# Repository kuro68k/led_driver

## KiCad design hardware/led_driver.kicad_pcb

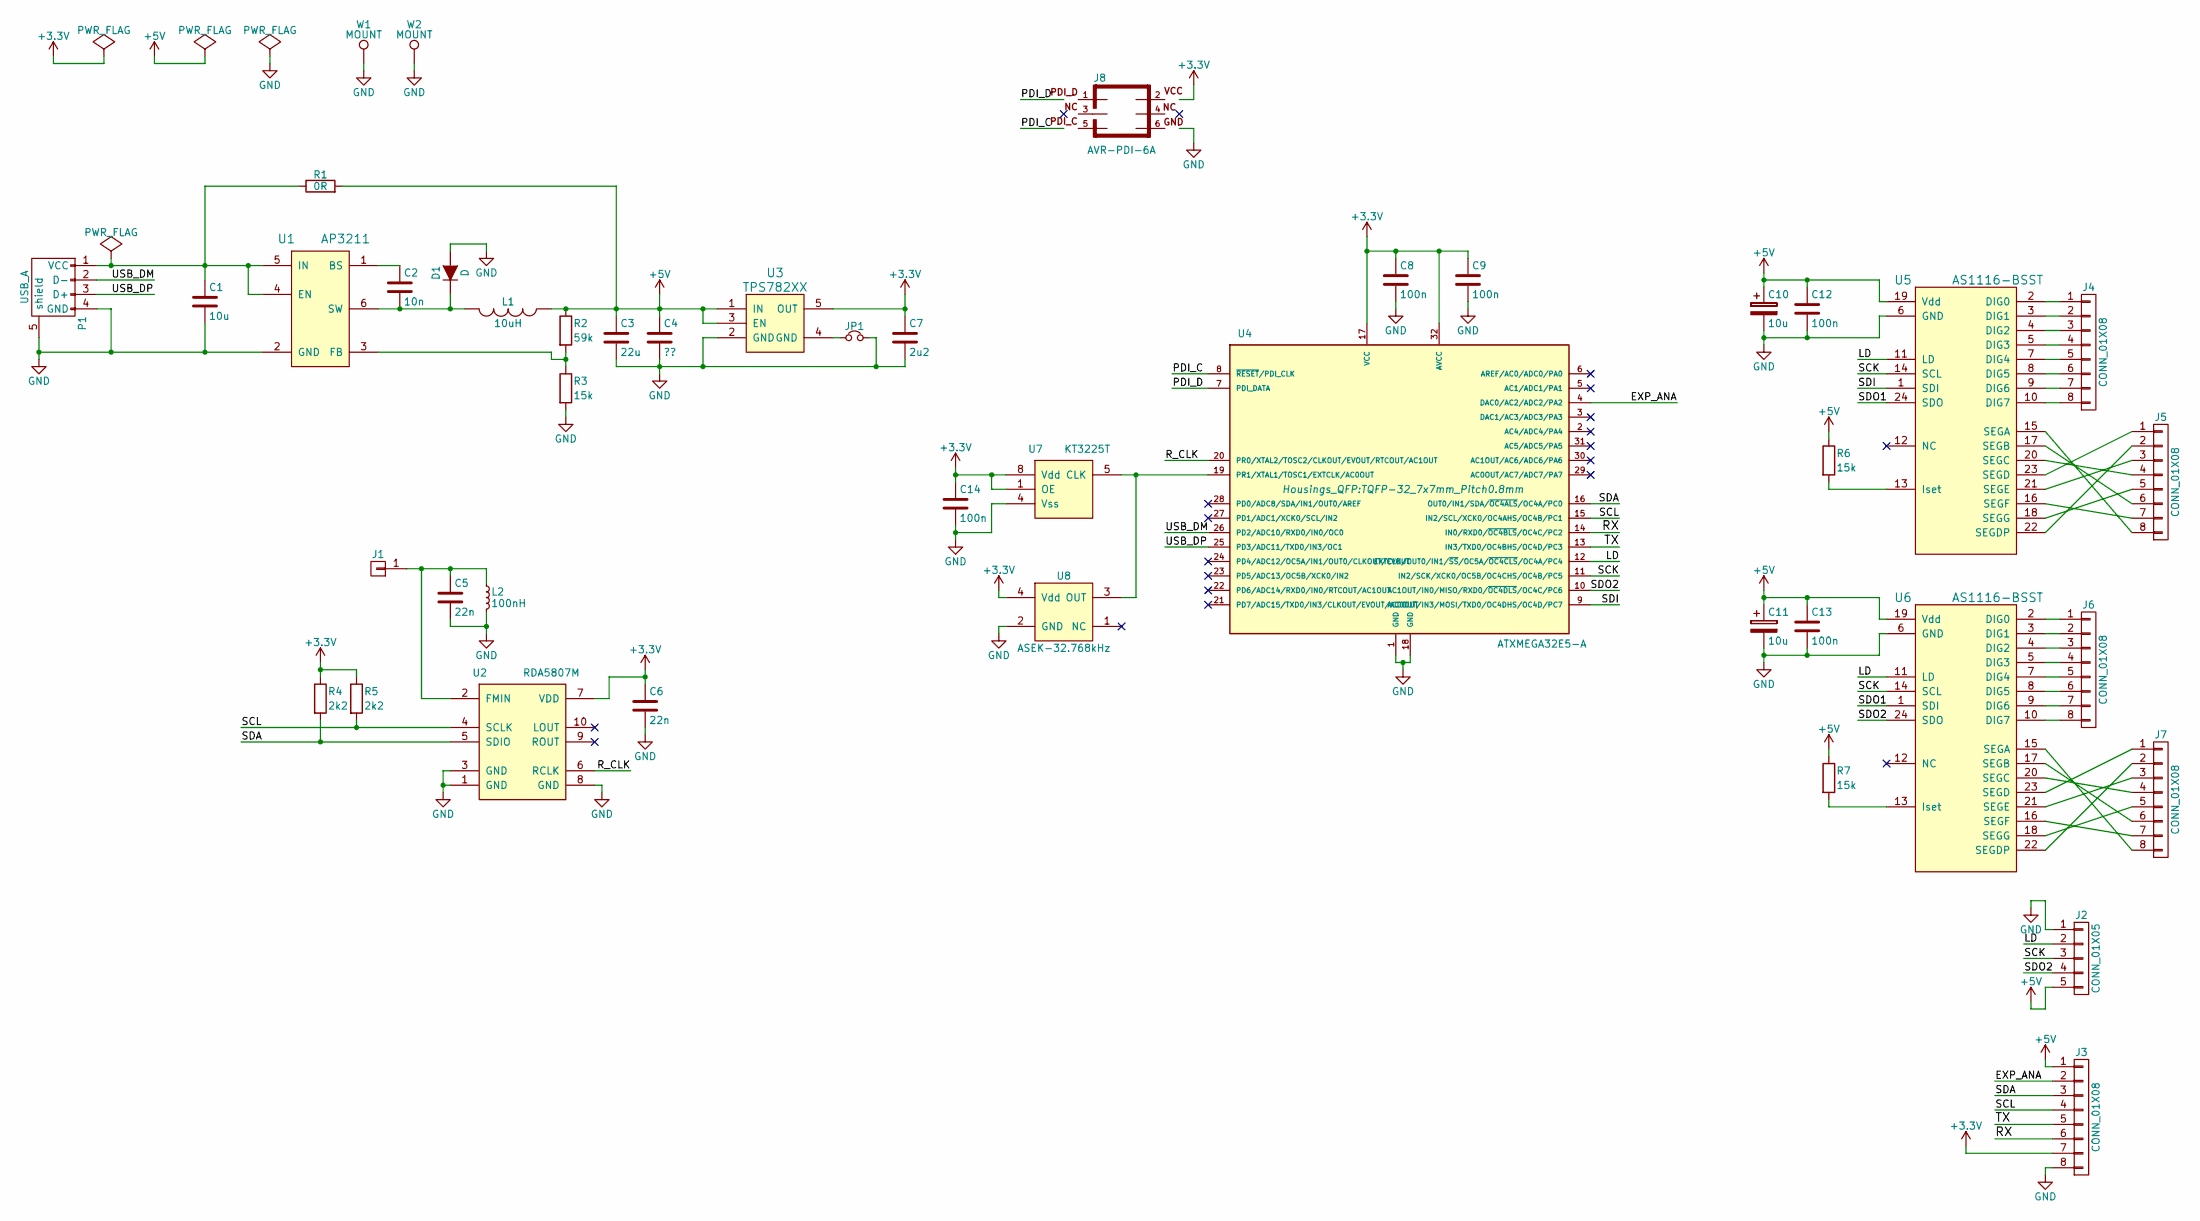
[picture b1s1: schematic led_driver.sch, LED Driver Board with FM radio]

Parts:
C1: 10u; C_0805
C2: 10n; C_0603
C3: 22u; C_0603
C4: ??; C_0603
C5, C6: 22n; C_0603
C7: 2u2; C_0603
C8, C9, C12, C13, C14: 100n; C_0603
C10, C11: 10u; SMD-1206_Pol
D1: D; SOD-323_HandSoldering
J1: CONN_01X01; Pin_Header_Straight_1x01
J2: CONN_01X05; B5B-ZR-SM4-TF
J3, J4, J5, J6, J7: CONN_01X08; B8B-ZR-SM4-TF
J8: AVR-PDI-6A; 3x2_1.27mm_SMD_header
JP1: Jumper_NC_Small; R_0603
L1: 10uH; Neosid_Inductor_SM-NE56_SMD2220
L2: 100nH; R_0603
P1: USB_A; Molex_47346-0001_Micro_USB_SMT
R1: 0R; R_0603
R2: 59k; R_0603
R3, R6, R7: 15k; R_0603
R4, R5: 2k2; R_0603
U1: AP3211; SOT-23-6
U2: RDA5807M; MSOP-10_3x3mm_Pitch0.5mm
U3: TPS782XX; SOT-23-5
U4: ATXMEGA32E5-A; TQFP-32_7x7mm_Pitch0.8mm
U5, U6: AS1116-BSST; SSOP-24_3.9x8.7mm_Pitch0.635mm
U7: KT3225T
U8: ASEK-32.768kHz; Crystal-3.2x2.5-ASEK-Series-Abracon
W1, W2: MOUNT; MountingHole_2.5mm_Pad

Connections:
+3V3: C6.1, C7.1, C8.1, C9.1, C14.1, J3.7, J8.2, R4.1, R5.1, U2.7 (VDD), U3.5 (OUT), U4.17 (VCC), U4.32 (AVCC), U7.1 (OE), U7.8 (Vdd), U8.4 (Vdd)
+5V: C3.1, C4.1, C10.1, C11.1, C12.1, C13.1, J2.5, J3.1, L1.1, R1.2, R2.1, R6.1, R7.1, U3.1 (IN), U3.3 (EN), U5.19 (Vdd), U6.19 (Vdd)
/EXP_ANA: J3.2, U4.4 (DAC0/AC2/ADC2/PA2)
/LD: J2.2, U4.12 (EXTCLK/OUT0/IN1/~SS~/OC5A/~OC4CLS~/OC4A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), U5.11 (LD), U6.11 (LD)
/PDI_C: J8.5, U4.8 (~RESET~/PDI_CLK)
/PDI_D: J8.1, U4.7 (PDI_DATA)
/RX: J3.6, U4.14 (IN0/RXD0/~OC4BLS~/OC4C/PC2)
/R_CLK: U2.6 (RCLK), U4.20 (PR0/XTAL2/TOSC2/CLKOUT/EVOUT/RTCOUT/AC1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)
/SCK: J2.3, U4.11 (IN2/SCK/XCK0/OC5B/OC4CHS/OC4B/PC5), U5.14 (SCL), U6.14 (SCL)
/SCL: J3.4, R5.2, U2.4 (SCLK), U4.15 (IN2/SCL/XCK0/OC4AHS/OC4B/PC1)
/SDA: J3.3, R4.2, U2.5 (SDIO), U4.16 (OUT0/IN1/SDA/~OC4ALS~/OC4A/PC0)
/SDI: U4.9 (AC0OUT/IN3/MOSI/TXD0/OC4DHS/OC4D/PC7), U5.1 (SDI)
/SDO1: U5.24 (SDO), U6.1 (SDI)
/SDO2: J2.4, U4.10 (AC1OUT/IN0/MISO/RXD0/~OC4DLS~/OC4C/PC6), U6.24 (SDO)
/TX: J3.5, U4.13 (IN3/TXD0/OC4BHS/OC4D/PC3)
/USB_DM: P1.2 (D-), U4.26 (PD2/ADC10/RXD0/IN0/OC0)
/USB_DP: P1.3 (D+), U4.25 (PD3/ADC11/TXD0/IN3/OC1)
GND: C1.2, C3.2, C4.2, C5.2, C6.2, C7.2, C8.2, C9.2, C10.2, C11.2, C12.2, C13.2, C14.2, D1.2 (A), J2.1, J3.8, J8.6, JP1.2, L2.2, P1.4 (GND), P1.5 (shield), R3.2, U1.2 (GND), U2.1 (GND), U2.3 (GND), U2.8 (GND), U3.2 (GND), U4.1 (GND), U4.18 (GND), U5.6 (GND), U6.6 (GND), U7.4 (Vss), U8.2 (GND), W1.1, W2.1
unnamed: C1.1, P1.1 (VCC), R1.1, U1.4 (EN), U1.5 (IN)
unnamed: C2.1, U1.1 (BS)
unnamed: C2.2, D1.1 (K), L1.2, U1.6 (SW)
unnamed: C5.1, J1.1, L2.1, U2.2 (FMIN)
unnamed: J4.1, U5.2 (DIG0)
unnamed: J4.2, U5.3 (DIG1)
unnamed: J4.3, U5.4 (DIG2)
unnamed: J4.4, U5.5 (DIG3)
unnamed: J4.5, U5.7 (DIG4)
unnamed: J4.6, U5.8 (DIG5)
unnamed: J4.7, U5.9 (DIG6)
unnamed: J4.8, U5.10 (DIG7)
unnamed: J5.1, U5.23 (SEGD)
unnamed: J5.2, U5.22 (SEGDP)
unnamed: J5.3, U5.21 (SEGE)
unnamed: J5.4, U5.20 (SEGC)
unnamed: J5.5, U5.18 (SEGG)
unnamed: J5.6, U5.17 (SEGB)
unnamed: J5.7, U5.16 (SEGF)
unnamed: J5.8, U5.15 (SEGA)
unnamed: J6.1, U6.2 (DIG0)
unnamed: J6.2, U6.3 (DIG1)
unnamed: J6.3, U6.4 (DIG2)
unnamed: J6.4, U6.5 (DIG3)
unnamed: J6.5, U6.7 (DIG4)
unnamed: J6.6, U6.8 (DIG5)
unnamed: J6.7, U6.9 (DIG6)
unnamed: J6.8, U6.10 (DIG7)
unnamed: J7.1, U6.23 (SEGD)
unnamed: J7.2, U6.22 (SEGDP)
unnamed: J7.3, U6.21 (SEGE)
unnamed: J7.4, U6.20 (SEGC)
unnamed: J7.5, U6.18 (SEGG)
unnamed: J7.6, U6.17 (SEGB)
unnamed: J7.7, U6.16 (SEGF)
unnamed: J7.8, U6.15 (SEGA)
unnamed: JP1.1, U3.4 (GND)
unnamed: R2.2, R3.1, U1.3 (FB)
unnamed: R6.2, U5.13 (Iset)
unnamed: R7.2, U6.13 (Iset)
unnamed: U4.19 (PR1/XTAL1/TOSC1/EXTCLK/AC0OUT), U7.5 (CLK), U8.3 (OUT)

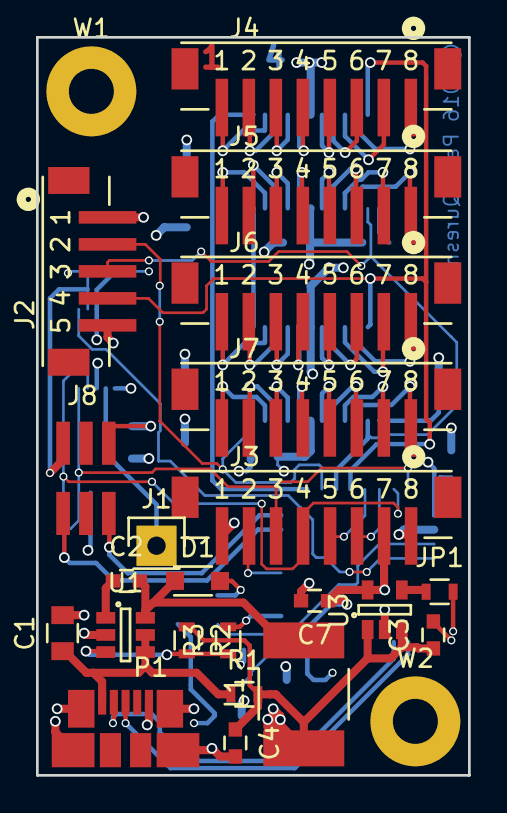
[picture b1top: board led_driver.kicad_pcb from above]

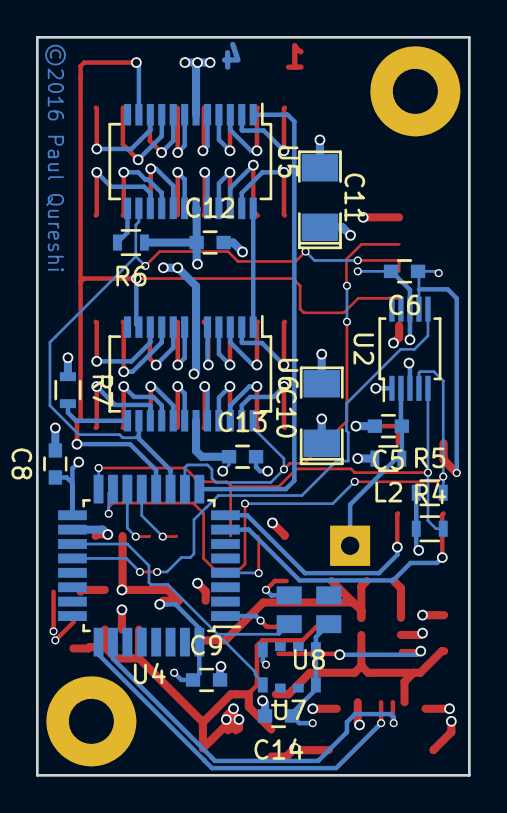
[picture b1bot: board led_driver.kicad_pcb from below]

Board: 4 copper layers, 24.0 x 41.0 mm, 44 parts (20 on the bottom side), 59 nets.

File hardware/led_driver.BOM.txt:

Title	LED Driver Board with FM radio
Date	27/11/2016 16:58:48
Source	led_driver.sch
Revsision	1.0
Company	Keio

Capacitors	7	X7R/X5R, 16V unless otherwise stated
	C1	10u		0805	
	C2	10n		0603	
	C3	22u		0603	
	C5, C6 	22n		0603	
	C7	2u2		0603	
	C8, C9, C12, C13, C14 	100n		0603	
	C10, C11 	10u		1206	

Diodes	1
	D1	Schottky	PMEG3015EJ	SOD-323	

Connectors	5
	J2	CONN_01X05		B5B-ZR-SM4-TF	
	J3	CONN_01X08		B8B-ZR-SM4-TF	
	J4, J5, J6, J7 	CONN_01X08		B8B-ZR-SM4-TF	
	J8	AVR-PDI-6A		3x2_1.27mm_SMD_header	
	J9	USB_A		Molex 47346-0001	

Inductors	2
	L1	10uH	LQH5BPN100MT0L	Neosid_Inductor_SM-NE56_SMD2220	
	L2	100nH		0603	

Resistors	4	1% unless otherwise stated
	R1	0R		0603	
	R2	59k		0603	
	R3, R6, R7 	15k		0603	
	R4, R5 	2k2		0603	

Integrated Circuits	7
	U1	AP3211		SOT-23	
	U2	RDA5807M		MSOP-10_3x3mm_Pitch0.5mm	
	U3	TPS782XX		SOT-23	
	U4	ATXMEGA32E5-A		TQFP-32	
	U5, U6 	AS1116-BSST		SSOP-24	
	U7	KT3225T		KT3225T	
	U8	ASEK-32.768kHz		Crystal-3.2x2.5-ASEK-Series-Abracon

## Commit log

2016-10-25 :boom::camel: Added .gitattributes & .gitignore files
2016-10-25 Added GPL licence
2016-11-11 Sorted out library references
2016-11-14 Preparing for production
2016-11-15 Ready for V1.0 release
    Converted schematic to A4 for ease of viewing
2016-11-27 BOM fixes
2017-04-13 BOM output updates
2017-07-29 RDA read OK
2017-08-13 Additional programming guides
2017-08-13 RDA working with Classic FM
2017-08-13 Data validation
2017-08-29 Improved FM scan
2017-08-31 Formatting
2017-08-31 Radio time mode
2017-09-07 Debug code cleanup

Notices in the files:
hardware/led_driver.kicad_pcb:
©2016 Paul Qureshi
